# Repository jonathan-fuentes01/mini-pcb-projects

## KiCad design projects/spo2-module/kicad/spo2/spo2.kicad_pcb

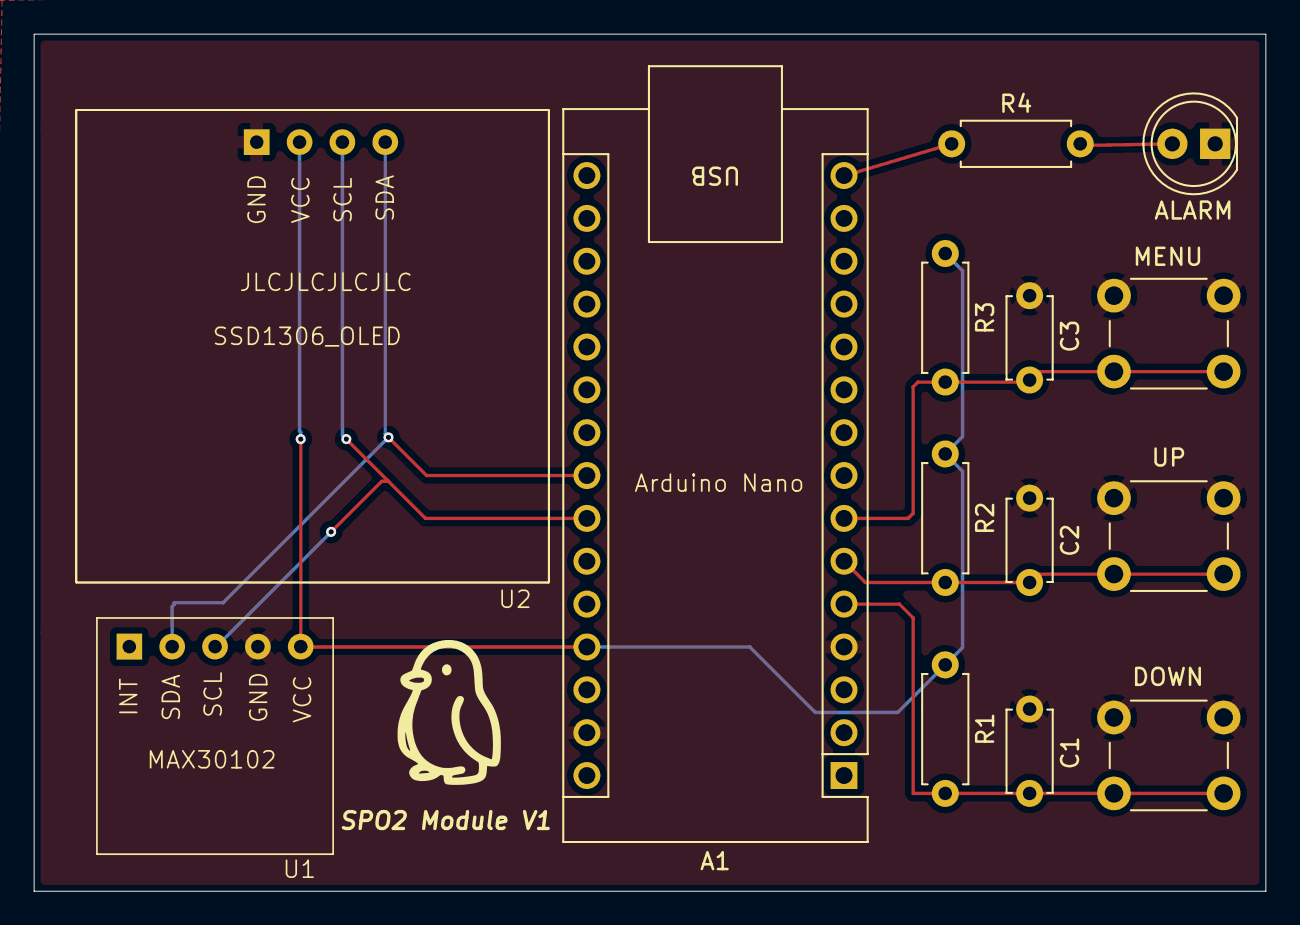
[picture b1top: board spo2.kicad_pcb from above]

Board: 2 copper layers, 73.0 x 50.8 mm, 14 parts (0 on the bottom side), 9 nets.

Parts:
A1: Arduino_Nano_v3.x; Arduino_Nano
ALARM: LED; LED_D5.0mm
C1, C2, C3: 100n; C_Disc_D4.7mm_W2.5mm_P5.00mm
DOWN: SW_Push; SW_PUSH_6mm
MENU: SW_Push; SW_PUSH_6mm
R1, R2, R3, R4: 1K; R_Axial_DIN0207_L6.3mm_D2.5mm_P7.62mm_Horizontal
U1: MAX30102; MAX30102_Module
U2: SSD1306
UP: SW_Push; SW_PUSH_6mm

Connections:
+5V: A1.27 (+5V), R1.1, R2.1, R3.1, U1.5 (VCC), U2.2 (VCC)
GND: A1.4 (GND), A1.29 (GND), ALARM.1 (K), C1.2, C2.2, C3.2, DOWN.1, MENU.1, U1.4 (GND), U2.1 (GND), UP.1
unnamed: A1.23 (A4), U1.2 (SDA), U2.4 (SDA)
unnamed: A1.24 (A5), U1.3 (SCL), U2.3 (SCL)
unnamed: A1.5 (D2), C1.1, DOWN.2, R1.2
unnamed: A1.6 (D3), C2.1, R2.2, UP.2
unnamed: A1.7 (D4), C3.1, MENU.2, R3.2
unnamed: A1.15 (D12), R4.1
unnamed: ALARM.2 (A), R4.2

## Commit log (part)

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2026-06-06 Added KiCAD files, and respective folders for mini projects
2026-06-06 Added 3d render and spo2 pictures
2026-06-06 Added firmware skeleton for the spo2 module
2026-06-09 Added files for the SSD1306 and MAX30102 module
2026-06-18 Added baremetal headers and files
2026-06-18 Added switches files, included initializations for switches and max30102 i2c
2026-06-18 Added UART and changed main initialization
2026-06-18 Added LED initializations
2026-06-18 Added read register function for max30102 and added fifo read function prototype
2026-06-30 Completed read byte function and FIFO read function for MAX30102 SP02 mode
